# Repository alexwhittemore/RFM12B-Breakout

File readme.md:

The RFM12B is a pretty popular basic, low-cost RF module. It lets you transmit a FIFO, receive a FIFO, and handles all the RF to do it. It also comes in an SMD package with a 2mm pin pitch, instead of 2.54/100mil. With this PCB, you can breadboard prototype with it.

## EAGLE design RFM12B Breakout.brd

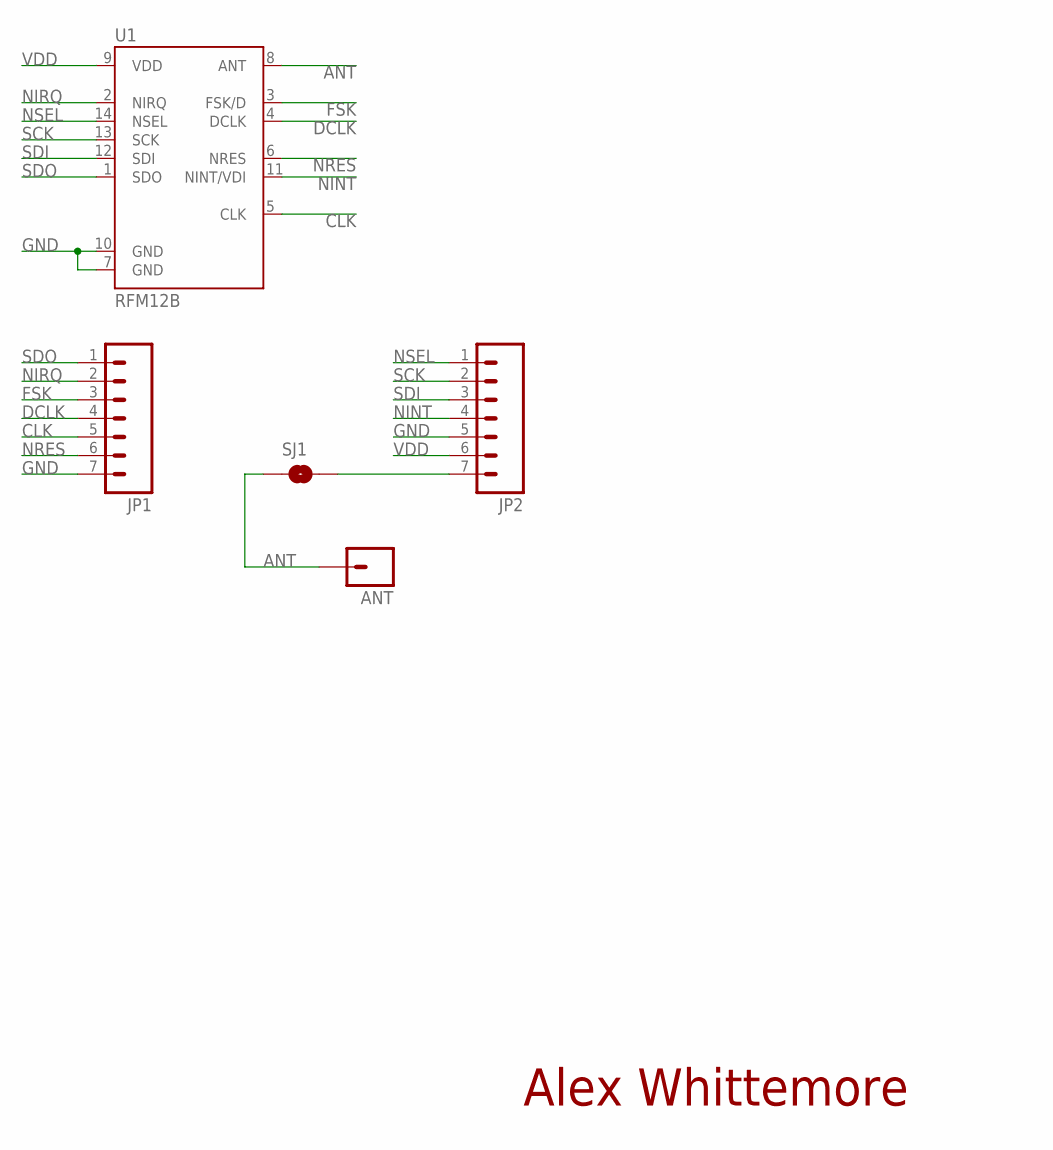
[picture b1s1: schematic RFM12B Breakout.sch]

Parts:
ANT: M01PTH; 1X01
JP1, JP2: M07LOCK; 1X07_LOCK
SJ1: SOLDERJUMPERNO; SJ_2S-NO
U1: RFM12B; RFM12-XXX-S2

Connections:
ANT: ANT.1, SJ1.1, U1.8 (ANT)
CLK: JP1.5, U1.5 (CLK)
DCLK: JP1.4, U1.4 (DCLK)
FSK: JP1.3, U1.3 (FSK/D)
GND: JP1.7, JP2.5, U1.7 (GND), U1.10 (GND)
unnamed: JP2.7, SJ1.2
NINT: JP2.4, U1.11 (NINT/VDI)
NIRQ: JP1.2, U1.2 (NIRQ)
NRES: JP1.6, U1.6 (NRES)
NSEL: JP2.1, U1.14 (NSEL)
SCK: JP2.2, U1.13 (SCK)
SDI: JP2.3, U1.12 (SDI)
SDO: JP1.1, U1.1 (SDO)
VDD: JP2.6, U1.9 (VDD)

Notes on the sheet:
Alex Whittemore

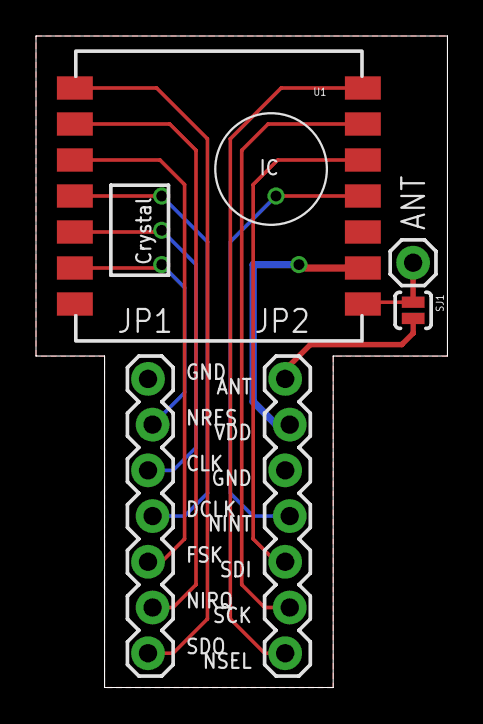
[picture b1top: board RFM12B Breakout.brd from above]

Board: 2 copper layers, 22.9 x 36.2 mm, 6 parts (1 on the bottom side), 14 nets.

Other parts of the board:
U$1: OSHW-LOGO-M

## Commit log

2012-09-17 Initial commit. Board should be ready to go, but I'm going to add some things.
2012-09-17 Added a readme.
2012-09-17 Edited silkscreen text to ensure minimum 5mil width for OSHPark.
2012-09-17 Beefed up the power trace to 16mil as it should have been all along. Probably not a problem in R1, but definitely something to touch up.
2013-06-20 Added .epf to gitignore

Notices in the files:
RFM12B Breakout.brd:
CC BY-SA 3.0
Some parts CC-BY-SA
parts and their libraries:
SparkFun-Connectors: Licensing: CC v3.0 Share-Alike You are welcome to use this library for commercial purposes.
AlexW-Eagle-Libraries: Released under the Creative Commons
AlexW-Eagle-Libraries: http://creativecommons.org/licenses/by-sa/3.0
